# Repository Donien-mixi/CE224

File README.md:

# Xe hai bánh tự cân bằng (TWIP) — STM32F411 + BMI160 + ESP32-S3

Đồ án điều khiển xe hai bánh tự cân bằng: STM32 giữ thăng bằng và chạy quỹ đạo ở 200 Hz, ESP32-S3
làm gateway Wi-Fi có trang điều khiển và ghi log, Scilab mô phỏng lại đúng phần luật điều khiển
đang nạp trên xe.

**Bản phát hành hiện hành: STM32 `RT47-SLIM` + ESP32 `NET47` (21/11/2026)** — **hoàn tất dọn code, không
đổi hành vi điều khiển** so với RT45 (tách nốt governor ra `.c`, xoá PID + 2 header chết + 6 test legacy): ba mức tốc độ **50 / 80 / 90 cm/s**, bù lệch bánh trái, cua
**0,72 m/s** ở cả hai chiều, chống trôi khi đứng yên, xuất phát mượt, đổi hướng liên tục, không ngập
ngừng khi phanh, không cắt motor khi bị giữ, **UART 921600, tự chọn/đổi kênh Wi-Fi, log mang theo chất
lượng sóng, trần MAX 90 theo duty**.
RT47 nạp bằng IDE từ source; **không còn gói nhị phân trong repo**. Muốn quay lui thì `git checkout <commit>`
rồi Build/Upload lại.
Trạng thái và việc còn mở: [`HANDOFF.md`](HANDOFF.md).

## 1. Kiến trúc

| Khối | Nội dung |
|---|---|
| STM32F411CEU6 | Vòng điều khiển 200 Hz (TIM4). BMI160 qua I2C, hai encoder GA25, PWM cho hai driver A4950. Luật lực R12 (14 trạng thái quan sát, K = 9.1508 / 6.1289 / 14.3279 / 1.1605) — **đóng băng**. Ba mức 0,50 / 0,80 / 0,90 m/s, 8 hướng. |
| Lớp giám sát | `balance_startup` (dựng từ 60°), `balance_recovery` (REC1), `balance_governor` (dự phòng mô-men, **neo mốc chỉ khi bão hoà**, phanh nhả 0,85 m/s²), `balance_interlock` (trần tốc độ), `balance_motion` / `balance_turn` (quỹ đạo, mốc vị trí/hướng, **trần cua 0,87 − \|w\|·0,131 → 0,719 m/s**, **nhả mốc khi đứng yên**), `balance_trim` (**bù lệch bánh trái**). Không đổi gain/observer/phân bổ lực R12. |
| ESP32-S3 | SoftAP `TWIP_RACER_S3` / `12345678`, HTTP :80, WebSocket :81, UART1 115200 (GPIO18/17). Trang `/ui/r12`, log 122 byte/khung, 40 cột, 50 Hz; TX WiFi 11 dBm; **chỉ ghi Flash khi xe đã dừng**. |
| Scilab + GCC | Mô phỏng dùng **chính header C của firmware**; đường đặc tính bánh fit lại từ log xe thật (lệch 1–2 %). |
| KiCad | Bo chuyển tiếp 160 × 65 mm, một mặt đồng B.Cu, 31 dây cầu. |

## 2. Firmware phát hành

| Bản | Board | Build ID | Tệp |
|---|---|---|---|
| **RT47-SLIM / NET47** (bản hiện hành) | STM32 | `BAL-20261121-R12-8DIR-RT47-SLIM` | nạp bằng IDE (Clean → Build → Run) |
| | ESP32-S3 | `TWIP-WEB-20261121-BAL-R12-8DIR-RT47-SLIM-NET47` | nạp bằng Arduino IDE (Upload) |

- Hash đầy đủ: `SHA256.json` trong từng thư mục; hash **20 tệp nguồn đã sinh ra binary**:
  `SOURCE_SHA256.json` (RT45).
- Hai board phải nạp cùng bản: gateway đối chiếu build ID với STM32, lệch là khoá điều khiển.
- Cách nạp: STM32CubeIDE (**Clean** → **Build** → **Run**) và Arduino IDE (**Upload**) — xem
  [`Docs/Nap_Bang_IDE.md`](Docs/Nap_Bang_IDE.md). Quay lui: `git checkout <commit>` rồi nạp lại.

## 3. Cấu trúc repo

| Thư mục | Nội dung |
|---|---|
| `Xe_Can_Bang/` | Project STM32CubeIDE. Luật điều khiển và giám sát ở `Core/Inc/balance_*.h`, FSM và vòng 200 Hz ở `Core/Src/robot_fsm.c`. |
| `ESP32_S3_Gateway/` | Sketch Arduino + trang web (`dashboard_html.h`), giao thức UART, phiên điều khiển, log RAM/Flash. |
| `Simulation/` | Mô hình Scilab, harness native dùng chung header firmware, bộ 36 ca kiểm tra, cấu hình plant. |
| `tools/` | **38 host test** (38 tệp `test_*.cjs`), script chạy mô phỏng, tải log cứu hộ. Mock gateway cho route test ở `tools/lib/gateway_mock.cjs`. |
| *(không còn)* | Gói nhị phân đã xoá; firmware nạp bằng IDE, bản cũ nằm trong git history. |
| `Hardware/` | Schematic, PCB KiCad, thư viện footprint, tài liệu lắp ráp. |
| `Docs/` | Tài liệu thiết kế + báo cáo các vòng RT22 → RT45 (danh sách ở mục 7). |

## 4. Chạy nhanh

```powershell
# Kiểm thử trên máy (cần Node.js; test biên dịch C cần GCC tại C:/msys64/ucrt64/bin)
Get-ChildItem tools/test_*.cjs | ForEach-Object { node $_.FullName }

# Mô phỏng native: 12 ca tốc độ / 12 ca biên / 12 ca khởi hành 50 cm/s, mỗi ca 20 s
node tools/run_governor_sim.cjs --stress
node tools/run_governor_sim.cjs --stress --edge
node tools/run_governor_sim.cjs --stress --launch --launch50
```

- **STM32:** mở `Xe_Can_Bang/` bằng STM32CubeIDE → Build → Run (ST-LINK), hoặc nạp thẳng `.hex`.
- **ESP32:** mở `ESP32_S3_Gateway/ESP32_S3_Gateway.ino` bằng Arduino IDE (board ESP32S3 Dev Module,
  Flash 16 MB, partition 3 MB APP/9.9 MB FATFS, PSRAM OPI, USB CDC on boot) → Upload.
- **Scilab:** chạy `Simulation/build_native.ps1` rồi Execute `robot_can_bang_pid_1.sce` ở gốc repo.

## 5. Đã kiểm chứng

| Hạng mục | Kết quả | Điều kiện |
|---|---|---|
| Host test | **42/42 pass** | Node.js 24, GCC (msys2); mỗi test tự biên dịch phần C tương ứng |
| Mô phỏng native | **36/36 ca đủ 20/20 s** khi chọn mức ≤ 80 (12 stress80 + 12 edge + 12 launch); **35/36** khi chạy MAX 90 | Ca còn lại là pin 11,2 V — đúng vùng bị cấm với mức 90; chạy lại sau RT39, số liệu trùng RT38 |
| Log xe thật | RT36: 154 s. RT38: 84 s. RT39: **8 log, 1 100 s** (3 lần ngã ở 90, 1 lần cắt motor khi bị giữ) → cơ sở của RT40. RT40 **chưa có log**; RT41 có log 50 s (đường lệnh ổn định, không lần nào >150 ms khi đang có lệnh); RT42 có log 148 s tại nhà (đường lệnh đạt p95 27 ms; 2 lần ngã ở MAX 90 → RT43 sửa); RT43 chưa có log | Pack 11,7 V; xem `Docs/RT36_Sua_4_Loi.md`, `Docs/RT37_Xuat_Phat_Muot.md` |
| Nguồn ↔ binary | 13/13 tệp khớp `SOURCE_SHA256.json` | Hash tính lại tại máy này, 18/11/2026 |

## 6. Giới hạn đã biết

- **Trần tốc độ thực ~0,96 m/s** (đo tại 11,7 V). Mức 0,90 chỉ dùng khi pin **≥ 12,0 V**; dưới
  ~11,9 V governor sẽ ghìm. Muốn nhanh hơn phải lên **4S** hoặc đổi motor/giảm tốc.
- **Cua ở MAX 90 tự hạ về ~0,75 m/s** (trần cua RT36) — cố ý, để bánh ngoài còn dư và hai chiều
  cua đối xứng; chạy thẳng vẫn 0,90 m/s.
- Bù lệch bánh trái (110 PWM) cân mô-men nhưng không làm bánh trái khoẻ thêm; cua trái vẫn ngả
  nhiều hơn cua phải (phần cơ khí).
- Buông ga/đảo chiều đột ngột ở 0,85–0,90 m/s có thể làm xe ngã — cần giảm tốc trước khi đảo chiều.
- Firmware không có watchdog độc lập: nếu MCU treo, TIM1 giữ duty cuối.
- Mô hình mô phỏng chưa có trượt bánh, tụt áp theo tải và tư thế trung tính +1,5°.

## 7. Tài liệu

- [`HANDOFF.md`](HANDOFF.md) — trạng thái, quy tắc vận hành, việc còn mở.
- [`Docs/Tong_Quan_Do_An.md`](Docs/Tong_Quan_Do_An.md) — tổng quan đồ án.
- [`Docs/Tinh_Nang_Xe_Hien_Hanh.md`](Docs/Tinh_Nang_Xe_Hien_Hanh.md) — chức năng đang chạy, kèm số đo.
- [`Docs/Thuat_Toan_Dieu_Khien.md`](Docs/Thuat_Toan_Dieu_Khien.md) — luật điều khiển và các lớp giám sát.
- [`Docs/Thong_So_Xe_Hien_Tai.md`](Docs/Thong_So_Xe_Hien_Tai.md) — thông số cơ khí, điện, encoder, đường đặc tính bánh.
- [`Docs/Bang_Ma_Loi_Tu_Dong_Dung.md`](Docs/Bang_Ma_Loi_Tu_Dong_Dung.md) — mọi trường hợp firmware tự cắt motor.
- [`Docs/Phan_Cung_Va_Ket_Noi.md`](Docs/Phan_Cung_Va_Ket_Noi.md), [`Huong_Dan_Di_Day_Toan_Bo_He_Thong.md`](Huong_Dan_Di_Day_Toan_Bo_He_Thong.md) — phần cứng và đấu dây.
- [`Docs/Roadmap_Do_An.md`](Docs/Roadmap_Do_An.md), [`Docs/Phat_Trien_Tiep.md`](Docs/Phat_Trien_Tiep.md) — phương pháp và hướng tiếp.
- Báo cáo từng vòng: [`RT22`](Docs/RT22_Doi_Xung_Va_Be_Huong.md) · [`RT23`](Docs/RT23_Nut_That_Va_Loi_Toc_Do.md) ·
  [`RT24`](Docs/RT24_Taper_Nghieng_Quay_Trai.md) · [`RT27`](Docs/RT27_Tro_Ve_Nen_RT21_Chong_Chiu.md) ·
  [`RT28`](Docs/RT28_Giu_Moc_Vi_Tri_Khi_Bi_Day.md) · [`RT29`](Docs/RT29_Tu_Ngat_4096.md) ·
  [`RT32`](Docs/RT32_Bo_Toc_Do_50_80_90.md) · [`RT33`](Docs/RT33_On_Dinh_Ket_Noi.md) ·
  [`RT34`](Docs/RT34_Cua_Muot.md) · [`RT35`](Docs/RT35_Mo_Phong_Khop_Log.md) ·
  [`RT36`](Docs/RT36_Sua_4_Loi.md) · [`RT37`](Docs/RT37_Xuat_Phat_Muot.md) · [`RT38`](Docs/RT38_Chuyen_Huong_Lien_Tuc.md) · [`RT39`](Docs/RT39_Cua_80_Khong_Khung.md) · [`RT40`](Docs/RT40_Het_Ngap_Ngung.md) · [`RT41`](Docs/RT41_Duong_Truyen.md) · [`RT42`](Docs/RT42_Song_2G4.md)
- [`Simulation/README.md`](Simulation/README.md), [`Hardware/README.md`](Hardware/README.md) — hướng dẫn riêng từng phần.

**Lịch sử phát triển** (RT7 → RT21, các bản nạp cũ, log thô và phân tích từng vòng) nằm trong **git
history** của repo, không giữ trong cây làm việc để repo gọn cho báo cáo.

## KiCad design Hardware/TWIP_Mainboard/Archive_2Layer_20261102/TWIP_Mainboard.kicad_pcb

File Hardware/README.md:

> **Trạng thái đồ án · 18/11/2026.** Nền R12 đã được thử cân bằng và dựng từ 60°. Điều khiển web có 8 hướng và log. Workspace đang ở **RT38-CONT / NET38**, đã build, kiểm thử trên máy và push Git. Mô hình tính pin kê thêm 10 mm. PCB một mặt đồng đã qua kiểm tra KiCad với 31 dây cầu. Xem [tổng quan và các việc còn mở](../Docs/Tong_Quan_Do_An.md).

> Các mô tả theo phiên bản cũ bên dưới là tài liệu đối chiếu. Dùng tổng quan phía trên để xác định cấu hình hiện hành.

> Bản hiện hành01/11/2026: PCBcarrier toàn bộ chân xuyên lỗ, bao gồm9tụ. Schematic đã gánfootprintTHT, đi dây lại; ERC/DRC/parity0. Xem TWIP_Mainboard/BOM_THT.md và ROUTING_CHECKS.json. Chưa phê duyệt sản xuất vì các xác nhận cơ khí/tải còn thiếu.

# Sơ đồ nguyên lý xe hai bánh tự cân bằng

Project KiCad **10.0**, sơ đồ revision **1.3**, cập nhật 30/10/2026.

## Mở project

1. Tải hoặc clone repo, giữ toàn bộ thư mục `Hardware`.
2. Mở `TWIP_Mainboard/TWIP_Mainboard.kicad_pro` trong KiCad.
3. Mở `TWIP_Mainboard.kicad_sch` để xem/sửa sơ đồ nguyên lý.

Giữ `TWIP_Modules.kicad_sym` và `sym-lib-table` cùng thư mục project. Thư viện được tham chiếu bằng `${KIPRJMOD}`, không phụ thuộc đường dẫn trên máy tác giả.

## Nội dung và phạm vi

- Năm bo/module có sẵn: STM32F411 Black Pill, ESP32-S3 N16R8, GY-BMI160, Dual A4950 và XL4015.
- Nguồn pin LiPo 3S, nguồn 5 V từ XL4015 và nguồn 3,3 V từ Black Pill.
- UART, I2C, PWM, hai giắc motor/encoder 6 dây và còi hai chân.
- INT1 BMI160 → STM32 PB2; còi (+) → PB12, còi (−) → GND: người dùng xác nhận đã nối trên breadboard.
- C1–C9 là tụ bổ sung để lắp trên PCB mới; breadboard hiện tại chưa có các tụ ngoài này. Tất cả tụ đều được đánh dấu sẽ lắp. Giá trị và vị trí theo tên các khung trong sơ đồ.
- Không thêm đầu nối ST-LINK riêng; dùng chân SWD có sẵn trên Black Pill.

Đây là sơ đồ **kết nối module**, không phải thiết kế lại mạch bên trong các module. Các tên chân logic của symbol module chưa phải số pad vật lý. Chưa gán footprint; cần xác minh đúng phiên bản bo, kích thước, khoảng cách và thứ tự chân trước khi làm PCB. `TWIP_Mainboard.kicad_pcb` đã có bản bố trí P0 150×60mm ngày31/10, nhưng chưa đi dây đồng do footprint/pad map module chưa xác minh. Xem [trạng thái PCB](TWIP_Mainboard/PCB_DRAFT.md); không dùng đặt sản xuất.

Sơ đồ đã kiểm tra bằng KiCad CLI: **0 lỗi, 0 cảnh báo ERC** khi bàn giao. Kết quả ERC không xác nhận kích thước module hoặc khả năng vận hành thực tế. Các tụ bổ sung cần được kiểm chứng với XL4015 và tải motor thực tế khi thử bo.

## Trạng thái firmware đi kèm repo

Commit Hardware ban đầu `d6a14af` chưa có firmware mới. Bản đồng bộ hiện tại của repo là STM32
**RT38-CONT** + ESP32 **NET38** (binary và hash trong `Firmware/RT36_SYM_20261118/`). Sơ đồ vẫn
là revision 1.3; việc đồng bộ source không xác nhận firmware đã nạp trên xe.

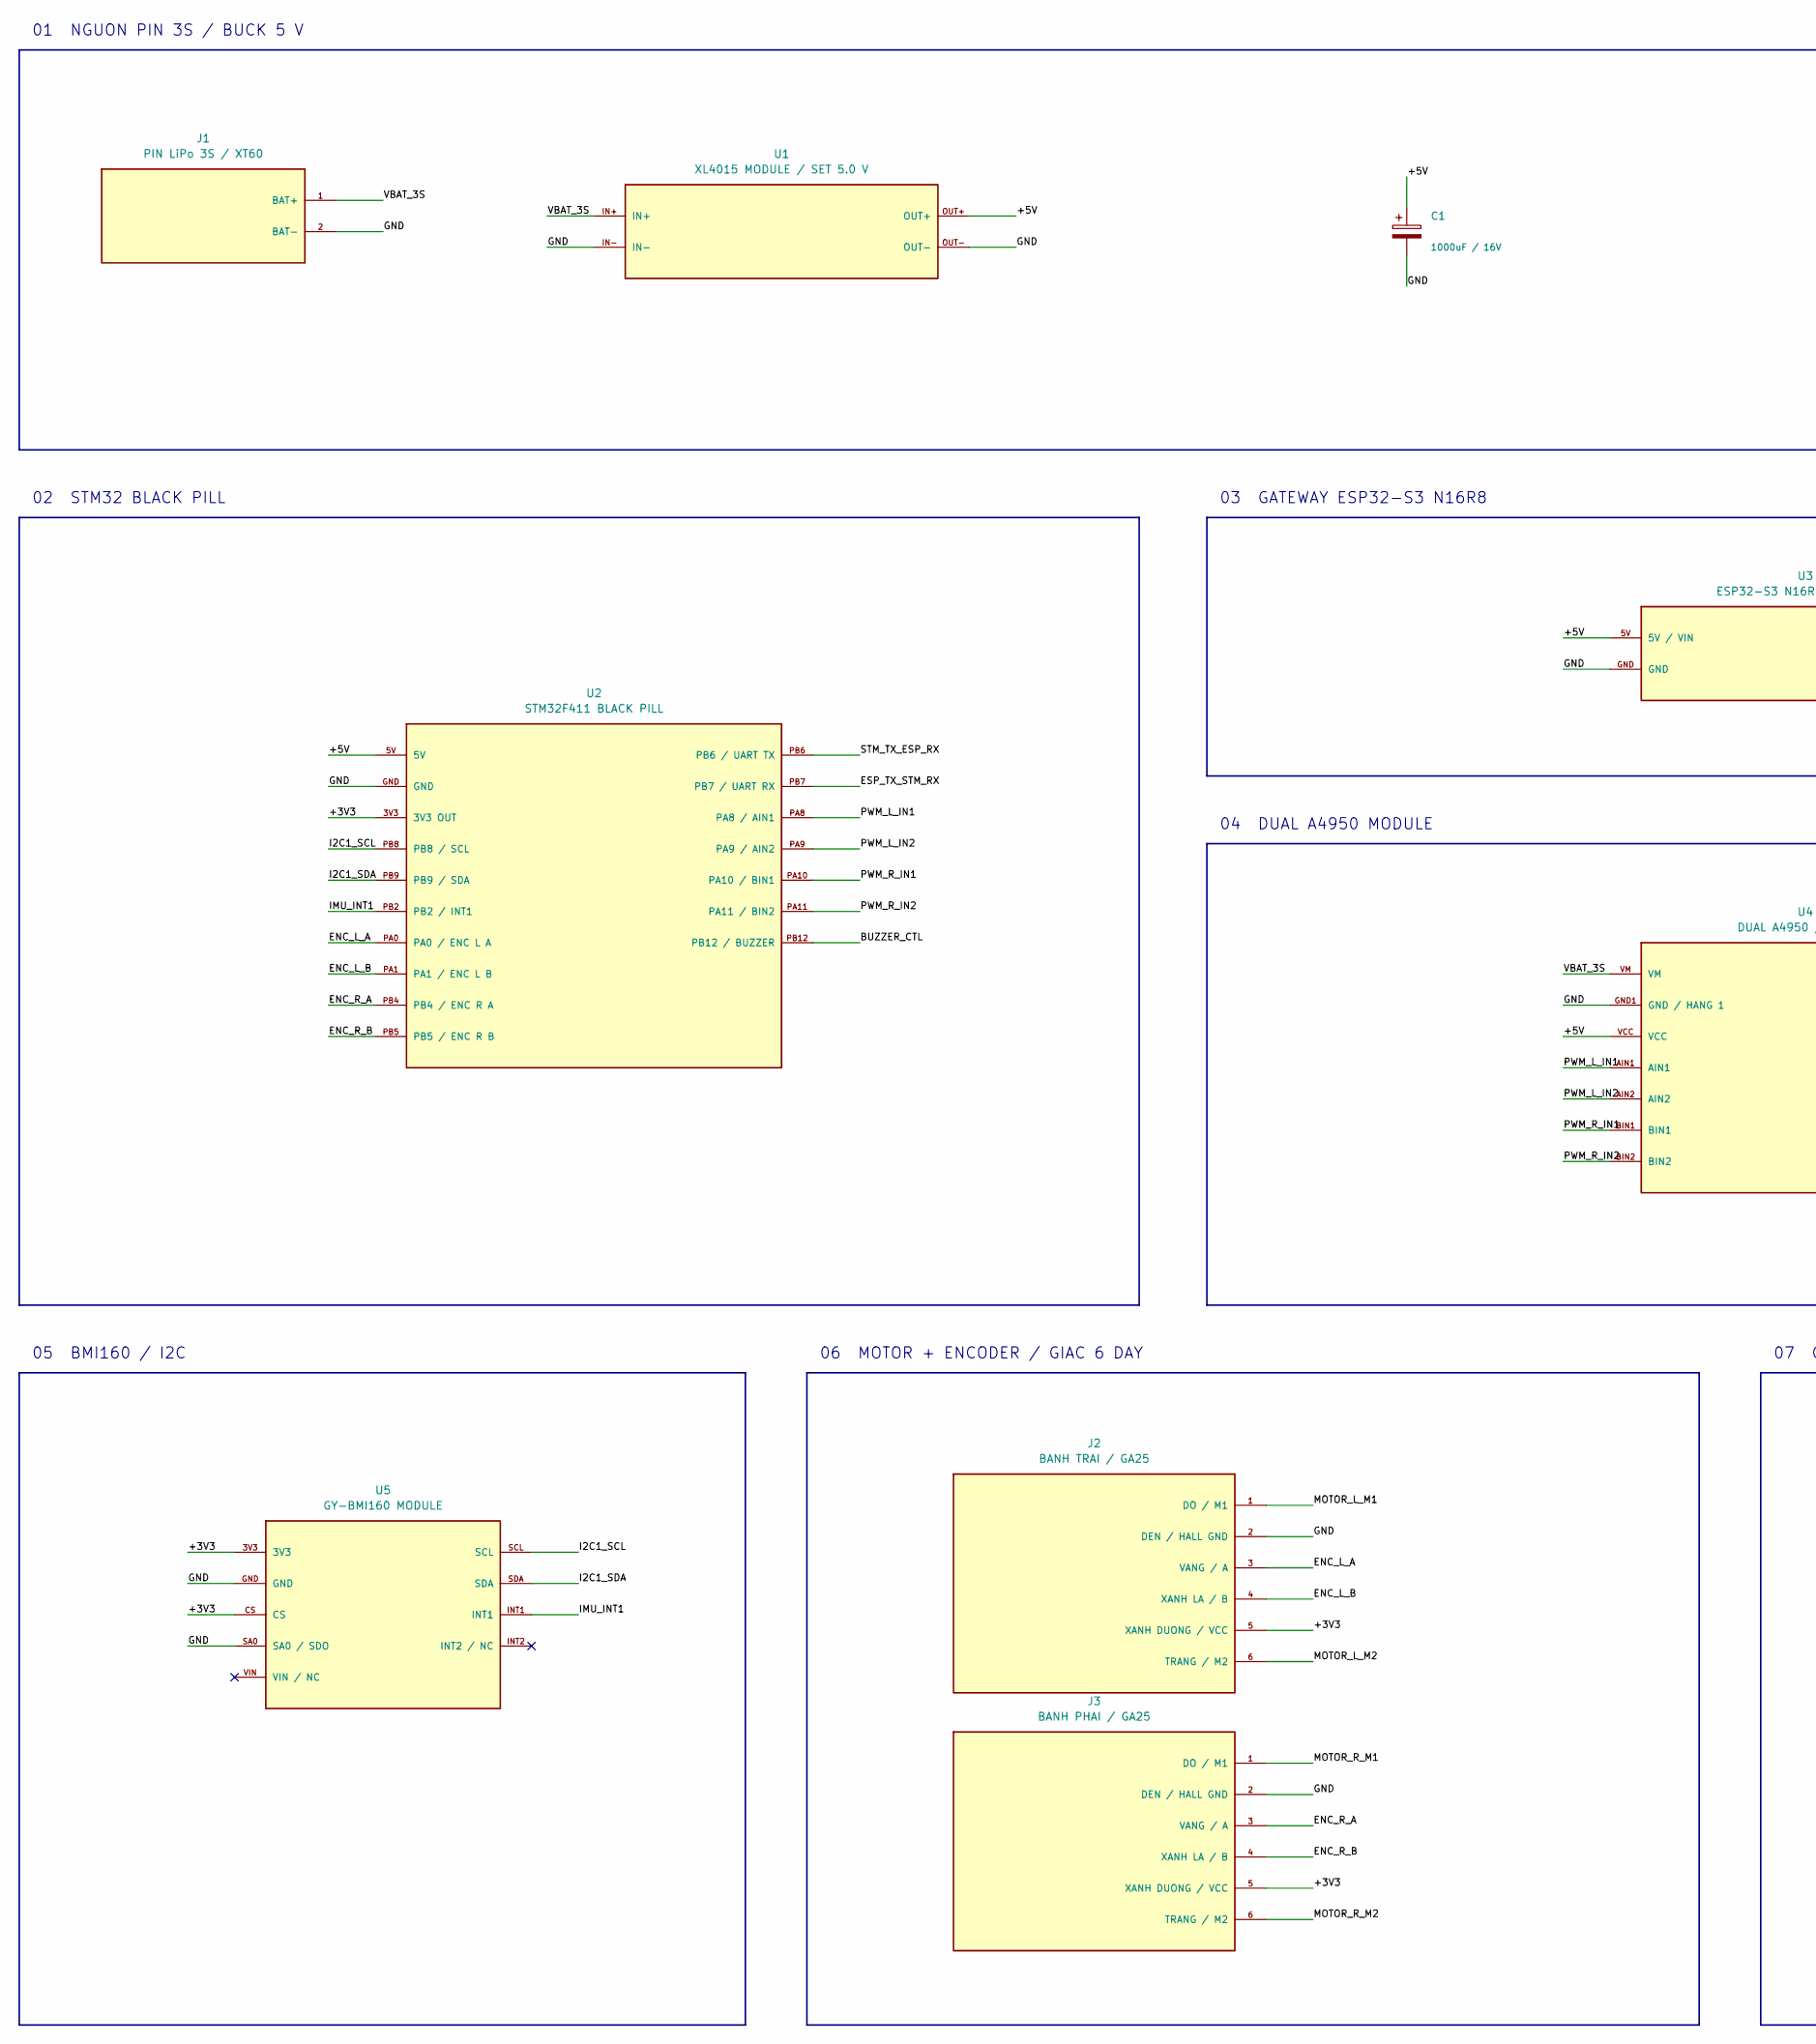
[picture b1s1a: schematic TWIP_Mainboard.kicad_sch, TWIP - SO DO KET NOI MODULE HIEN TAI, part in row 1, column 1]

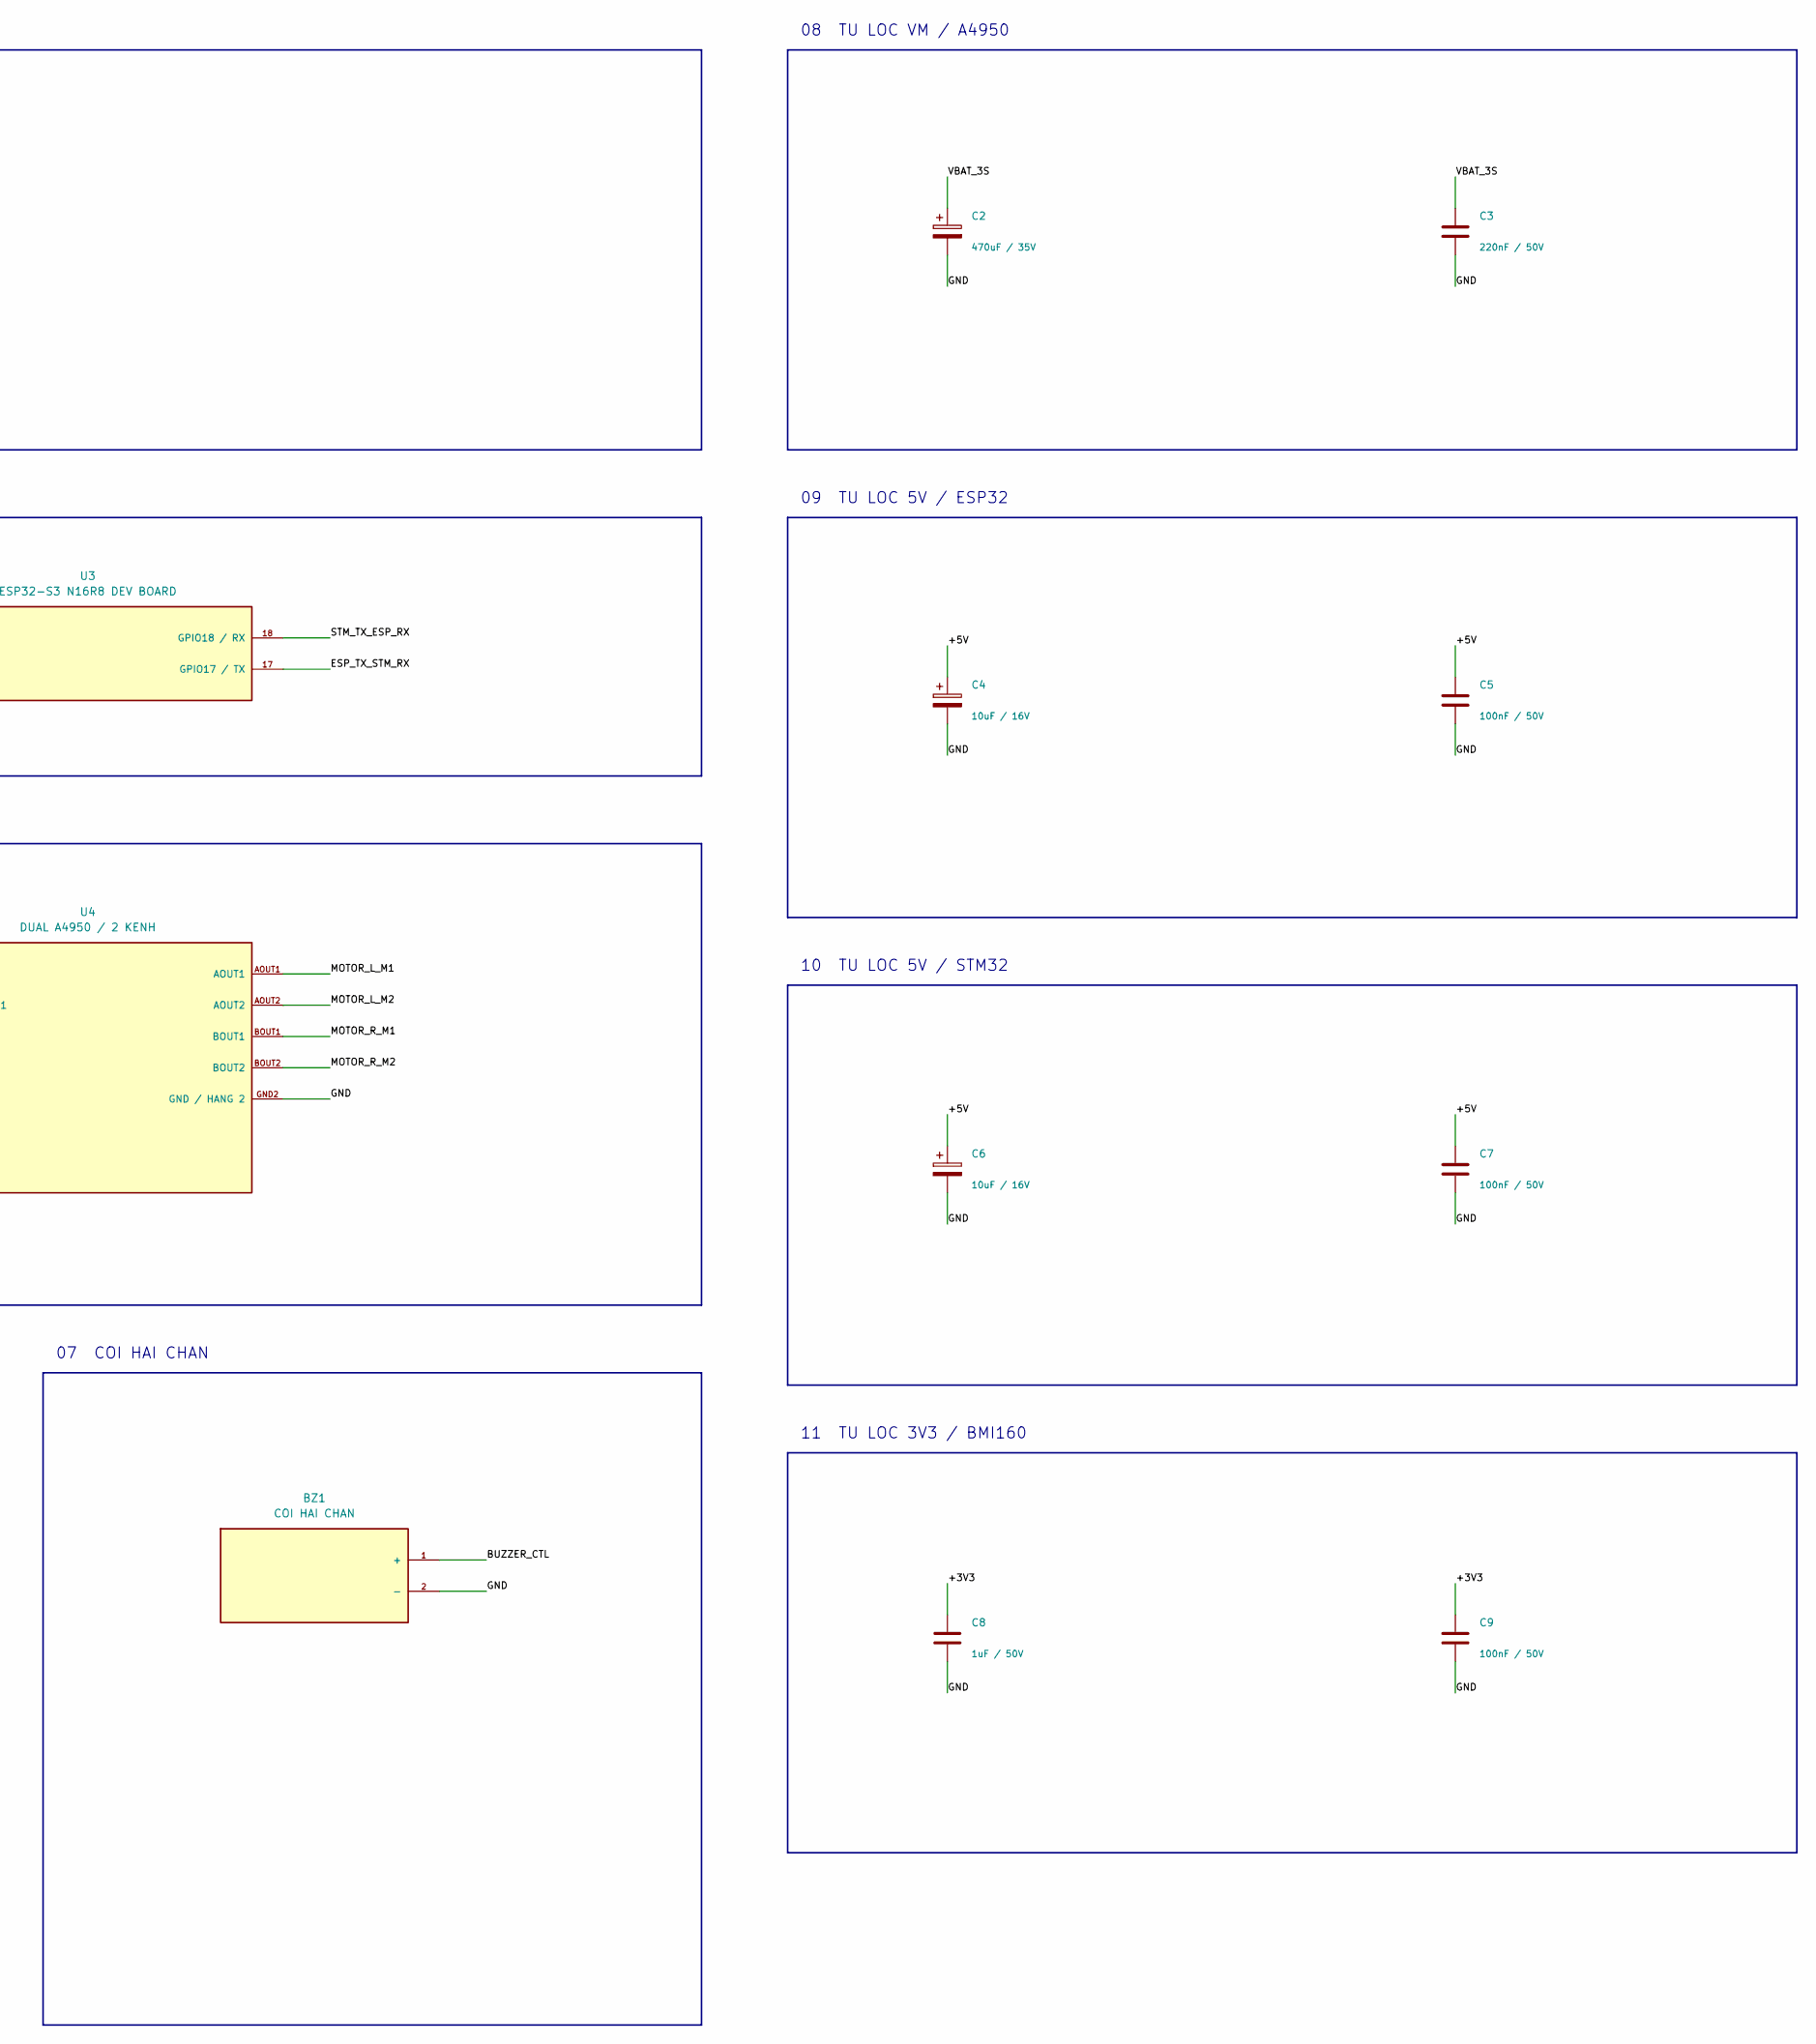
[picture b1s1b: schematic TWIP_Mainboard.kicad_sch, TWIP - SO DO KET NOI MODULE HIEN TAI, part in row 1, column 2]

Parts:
BZ1: COI HAI CHAN; Buzzer_Wire_1x02_2.54
C1: 1000uF / 16V; CP_Radial_D8.0mm_P5.00mm; MPN Shop radial D8x16 P5
C2: 470uF / 35V; Radial_D10_P5_SELECT_PART
C3: 220nF / 50V; C_Radial_MLCC_L6_W3.5_P5_THT
C4, C6: 10uF / 16V; CP_Radial_D4.0mm_P2.00mm; MPN IC4469 (shop SKU)
C5, C7, C9: 100nF / 50V; C_Radial_MLCC_L6_W3.5_P5_THT
C8: 1uF / 50V; C_Radial_MLCC_L6_W3.5_P5_THT
J1: PIN LiPo 3S / XT60; Battery_Terminal_2P_5.08
J2: BANH TRAI / GA25; Motor_1x06_2.54
J3: BANH PHAI / GA25; Motor_1x06_2.54
U1: XL4015 MODULE / SET 5.0 V; XL4015_Measured_50x20_Edge2
U2: STM32F411 BLACK PILL; BlackPill_WeAct_2x20_VERIFY
U3: ESP32-S3 N16R8 DEV BOARD; ESP32S3_2x22_Row25.5_VERIFY_MAP
U4: DUAL A4950 / 2 KENH; DualA4950_2x07_Row20_VERIFY_MAP
U5: GY-BMI160 MODULE; GY_BMI160_5plus7_Row10_VERIFY_MAP

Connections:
/+3V3: C8.1, C9.1, J2.5 (XANH DUONG / VCC), J3.5 (XANH DUONG / VCC), U2.3V3 (3V3 OUT), U5.3V3, U5.CS
/+5V: C1.1, C4.1, C5.1, C6.1, C7.1, U1.OUT+, U2.5V, U3.5V (5V / VIN), U4.VCC
/BUZZER_CTL: BZ1.1 (+), U2.PB12 (PB12 / BUZZER)
/ENC_L_A: J2.3 (VANG / A), U2.PA0 (PA0 / ENC L A)
/ENC_L_B: J2.4 (XANH LA / B), U2.PA1 (PA1 / ENC L B)
/ENC_R_A: J3.3 (VANG / A), U2.PB4 (PB4 / ENC R A)
/ENC_R_B: J3.4 (XANH LA / B), U2.PB5 (PB5 / ENC R B)
/ESP_TX_STM_RX: U2.PB7 (PB7 / UART RX), U3.17 (GPIO17 / TX)
/GND: BZ1.2 (-), C1.2, C2.2, C3.2, C4.2, C5.2, C6.2, C7.2, C8.2, C9.2, J1.2 (BAT-), J2.2 (DEN / HALL GND), J3.2 (DEN / HALL GND), U1.IN-, U1.OUT-, U2.GND, U3.GND, U4.GND1 (GND / HANG 1), U4.GND2 (GND / HANG 2), U5.GND, U5.SA0 (SA0 / SDO)
/I2C1_SCL: U2.PB8 (PB8 / SCL), U5.SCL
/I2C1_SDA: U2.PB9 (PB9 / SDA), U5.SDA
/IMU_INT1: U2.PB2 (PB2 / INT1), U5.INT1
/MOTOR_L_M1: J2.1 (DO / M1), U4.AOUT1
/MOTOR_L_M2: J2.6 (TRANG / M2), U4.AOUT2
/MOTOR_R_M1: J3.1 (DO / M1), U4.BOUT1
/MOTOR_R_M2: J3.6 (TRANG / M2), U4.BOUT2
/PWM_L_IN1: U2.PA8 (PA8 / AIN1), U4.AIN1
/PWM_L_IN2: U2.PA9 (PA9 / AIN2), U4.AIN2
/PWM_R_IN1: U2.PA10 (PA10 / BIN1), U4.BIN1
/PWM_R_IN2: U2.PA11 (PA11 / BIN2), U4.BIN2
/STM_TX_ESP_RX: U2.PB6 (PB6 / UART TX), U3.18 (GPIO18 / RX)
/VBAT_3S: C2.1, C3.1, J1.1 (BAT+), U1.IN+, U4.VM

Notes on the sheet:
01 NGUON PIN 3S / BUCK 5 V
02 STM32 BLACK PILL
03 GATEWAY ESP32-S3 N16R8
04 DUAL A4950 MODULE
05 BMI160 / I2C
06 MOTOR + ENCODER / GIAC 6 DAY
07 COI HAI CHAN
08 TU LOC VM / A4950
09 TU LOC 5V / ESP32
10 TU LOC 5V / STM32
11 TU LOC 3V3 / BMI160

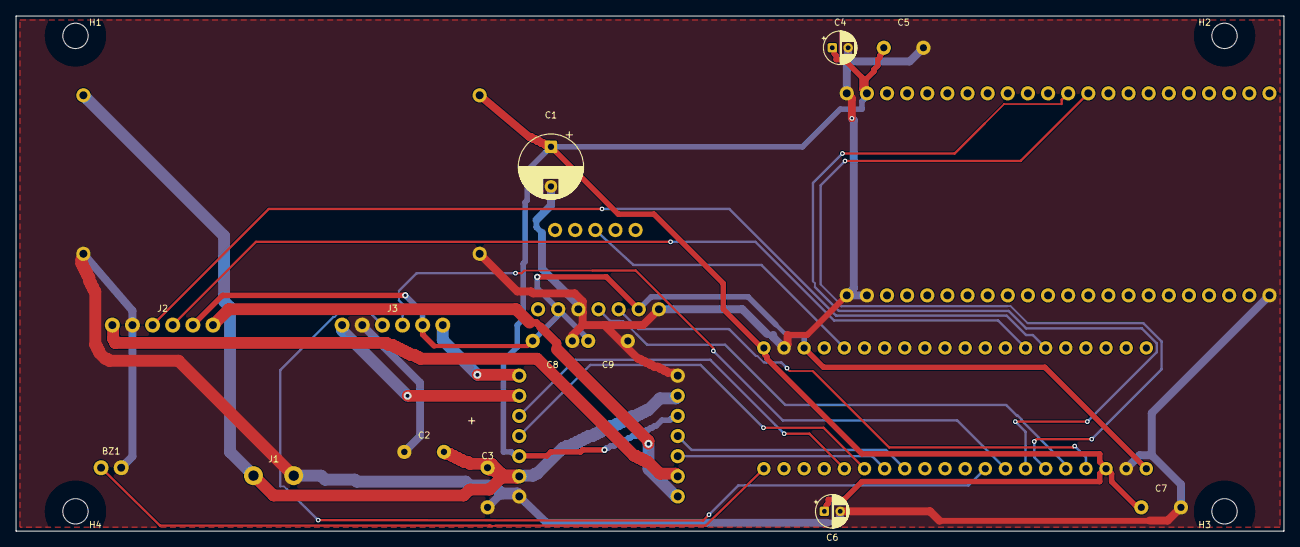
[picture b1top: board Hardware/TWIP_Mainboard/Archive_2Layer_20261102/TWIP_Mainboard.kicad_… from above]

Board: 2 copper layers, 160.0 x 65.0 mm, 22 parts (0 on the bottom side), 22 nets.

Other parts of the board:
H1, H2, H3, H4: M3 / 3.2mm NPTH; MountingHole_3.2mm_M3

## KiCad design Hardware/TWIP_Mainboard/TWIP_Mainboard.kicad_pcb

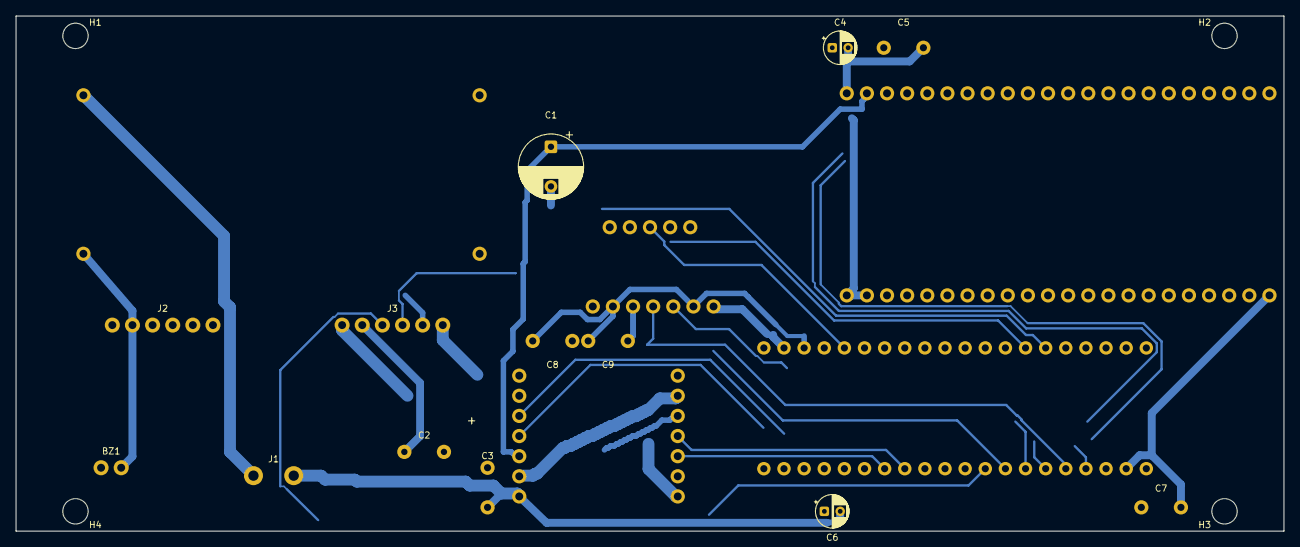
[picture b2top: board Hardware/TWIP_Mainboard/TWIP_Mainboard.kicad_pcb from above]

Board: 2 copper layers, 160.0 x 65.0 mm, 46 parts (0 on the bottom side), 22 nets.

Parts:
BZ1: COI HAI CHAN; Buzzer_Wire_1x02_2.54
C1: 1000uF / 16V; CP_Radial_D8.0mm_P5.00mm
C2: 470uF / 35V; Radial_D10_P5_SELECT_PART
C3: 220nF / 50V; C_Radial_MLCC_L6_W3.5_P5_THT
C4, C6: 10uF / 16V; CP_Radial_D4.0mm_P2.00mm
C5, C7, C9: 100nF / 50V; C_Radial_MLCC_L6_W3.5_P5_THT
C8: 1uF / 50V; C_Radial_MLCC_L6_W3.5_P5_THT
H1, H2, H3, H4: M3 / 3.2mm NPTH; MountingHole_3.2mm_M3
J1: PIN LiPo 3S / XT60; Battery_Terminal_2P_5.08
J2: BANH TRAI / GA25; Motor_1x06_2.54
J3: BANH PHAI / GA25; Motor_1x06_2.54
U1: XL4015 MODULE / SET 5.0 V; XL4015_Measured_50x20_Edge2
U2: STM32F411 BLACK PILL; BlackPill_WeAct_2x20_VERIFY
U3: ESP32-S3 N16R8 DEV BOARD; ESP32S3_2x22_Row25.5_VERIFY_MAP
U4: DUAL A4950 / 2 KENH; DualA4950_2x07_Row20_VERIFY_MAP
U5: GY-BMI160 MODULE; GY_BMI160_5plus7_Row10_VERIFY_MAP
W1: INSULATED SOLDER-SIDE WIRE /MOTOR_L_M2; SingleLayer_W1
W2: INSULATED SOLDER-SIDE WIRE /MOTOR_L_M1; SingleLayer_W2
W3: INSULATED SOLDER-SIDE WIRE /MOTOR_R_M1; SingleLayer_W3
W4: INSULATED SOLDER-SIDE WIRE /MOTOR_R_M2; SingleLayer_W4
W5: INSULATED SOLDER-SIDE WIRE /VBAT_3S; SingleLayer_W5
W7: INSULATED SOLDER-SIDE WIRE /+3V3; SingleLayer_W7
W8: INSULATED SOLDER-SIDE WIRE /+3V3; SingleLayer_W8
W9: INSULATED SOLDER-SIDE WIRE /+3V3; SingleLayer_W9
W10: INSULATED SOLDER-SIDE WIRE /+5V; SingleLayer_W10
W11: INSULATED SOLDER-SIDE WIRE /+5V; SingleLayer_W11
W12: INSULATED SOLDER-SIDE WIRE /+5V; SingleLayer_W12
W13: INSULATED SOLDER-SIDE WIRE /BUZZER_CTL; SingleLayer_W13
W14: INSULATED SOLDER-SIDE WIRE /ENC_L_A; SingleLayer_W14
W15: INSULATED SOLDER-SIDE WIRE /ENC_L_B; SingleLayer_W15
W16: INSULATED SOLDER-SIDE WIRE /ENC_R_A; SingleLayer_W16
W17: INSULATED SOLDER-SIDE WIRE /ENC_R_B; SingleLayer_W17
W18: INSULATED SOLDER-SIDE WIRE /ESP_TX_STM_RX; SingleLayer_W18
W19: INSULATED SOLDER-SIDE WIRE /ESP_TX_STM_RX; SingleLayer_W19
W20: INSULATED SOLDER-SIDE WIRE /I2C1_SDA; SingleLayer_W20
W21: INSULATED SOLDER-SIDE WIRE /PWM_L_IN1; SingleLayer_W21
W22: INSULATED SOLDER-SIDE WIRE /PWM_L_IN2; SingleLayer_W22
W23: INSULATED SOLDER-SIDE WIRE /STM_TX_ESP_RX; SingleLayer_W23
W24: INSULATED SOLDER-SIDE WIRE /STM_TX_ESP_RX; SingleLayer_W24
W26: INSULATED SOLDER-SIDE GND BRIDGE; SingleLayer_W26

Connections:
/+3V3: C8.1, C9.1, J2.5, J3.5, U2.3V3, U5.3V3, U5.CS, W7.1, W8.1, W9.1
/+5V: C1.1, C4.1, C5.1, C6.1, C7.1, U1.OUT+, U2.5V, U3.5V, U4.VCC, W10.1, W11.1, W12.1
/BUZZER_CTL: BZ1.1, U2.PB12, W13.1
/ENC_L_A: J2.3, U2.PA0, W14.1
/ENC_L_B: J2.4, U2.PA1, W15.1
/ENC_R_A: J3.3, U2.PB4, W16.1
/ENC_R_B: J3.4, U2.PB5, W17.1
/ESP_TX_STM_RX: U2.PB7, U3.17, W18.1, W19.1
/GND: BZ1.2, C1.2, C2.2, C3.2, C4.2, C5.2, C6.2, C7.2, C8.2, C9.2, J1.2, J2.2, J3.2, U1.IN-, U1.OUT-, U2.GND, U3.GND, U4.GND1, U4.GND2, U5.GND, U5.SA0, W26.1
/I2C1_SCL: U2.PB8, U5.SCL
/I2C1_SDA: U2.PB9, U5.SDA, W20.1
/IMU_INT1: U2.PB2, U5.INT1
/MOTOR_L_M1: J2.1, U4.AOUT2, W2.1
/MOTOR_L_M2: J2.6, U4.AOUT1, W1.1
/MOTOR_R_M1: J3.1, U4.BOUT1, W3.1
/MOTOR_R_M2: J3.6, U4.BOUT2, W4.1
/PWM_L_IN1: U2.PA8, U4.AIN1, W21.1
/PWM_L_IN2: U2.PA9, U4.AIN2, W22.1
/PWM_R_IN1: U2.PA10, U4.BIN1
/PWM_R_IN2: U2.PA11, U4.BIN2
/STM_TX_ESP_RX: U2.PB6, U3.18, W23.1, W24.1
/VBAT_3S: C2.1, C3.1, J1.1, U1.IN+, U4.VM, W5.1

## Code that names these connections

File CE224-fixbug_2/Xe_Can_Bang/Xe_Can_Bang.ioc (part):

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Mcu.Name=STM32F411C(C-E)Ux
Mcu.Package=UFQFPN48
Mcu.UserName=STM32F411CEUx
PA0-WKUP.Signal=S_TIM2_CH1_ETR
PA1.Signal=S_TIM2_CH2
PA10.Signal=S_TIM1_CH3
PA11.Signal=S_TIM1_CH4
PA13.Mode=Serial_Wire
PA13.Signal=SYS_JTMS-SWDIO
PA14.Mode=Serial_Wire
PA14.Signal=SYS_JTCK-SWCLK
PA8.Signal=S_TIM1_CH1
PA9.Signal=S_TIM1_CH2
PB12.GPIOParameters=GPIO_Label
PB12.GPIO_Label=BUZZER
PB12.Signal=GPIO_Output
PB2.GPIOParameters=GPIO_Label
PB2.GPIO_Label=BMI160_INT1
PB2.Signal=GPXTI2
PB4.Signal=S_TIM3_CH1
PB5.Signal=S_TIM3_CH2
PB6.Mode=Asynchronous
PB6.Signal=USART1_TX
PB7.Mode=Asynchronous
PB7.Signal=USART1_RX
PB8.Mode=I2C
PB8.Signal=I2C1_SCL
PB9.Mode=I2C
PB9.Signal=I2C1_SDA
PC13-ANTI_TAMP.GPIOParameters=PinState,GPIO_Label
PC13-ANTI_TAMP.GPIO_Label=LED_STATUS
PC13-ANTI_TAMP.PinState=GPIO_PIN_SET
PC13-ANTI_TAMP.Signal=GPIO_Output
PH0\ -\ OSC_IN.Mode=HSE-External-Oscillator
PH0\ -\ OSC_IN.Signal=RCC_OSC_IN
PH1\ -\ OSC_OUT.Mode=HSE-External-Oscillator
PH1\ -\ OSC_OUT.Signal=RCC_OSC_OUT
RCC.HSE_VALUE=25000000
RCC.SYSCLKFreq_VALUE=100000000
RCC.SYSCLKSource=RCC_SYSCLKSOURCE_PLLCLK
board=custom
